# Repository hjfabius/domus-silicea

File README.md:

## Introduction

The Domus Silicea project aims at providing an  integration platform for all things around home automation. 
It is designed to be as hardware/protocol-agnostic as possible. Domus Silicea brings together different bus systems, hardware devices and interface protocols by dedicated bindings. These bindings send and receive commands and status updates on the event bus. This concept allows designing user interfaces with a unique look&feel, but with the possibility to operate devices based on a big number of different technologies. 
Besides the user interfaces, it also brings the power of automation logics across different system boundaries.

## Trademark Disclaimer

Product names, logos, brands and other trademarks referred to within the Domus Silicea website are the property of their respective trademark holders. These trademark holders are not affiliated with Domus Silicea or our website. They do not sponsor or endorse our materials.

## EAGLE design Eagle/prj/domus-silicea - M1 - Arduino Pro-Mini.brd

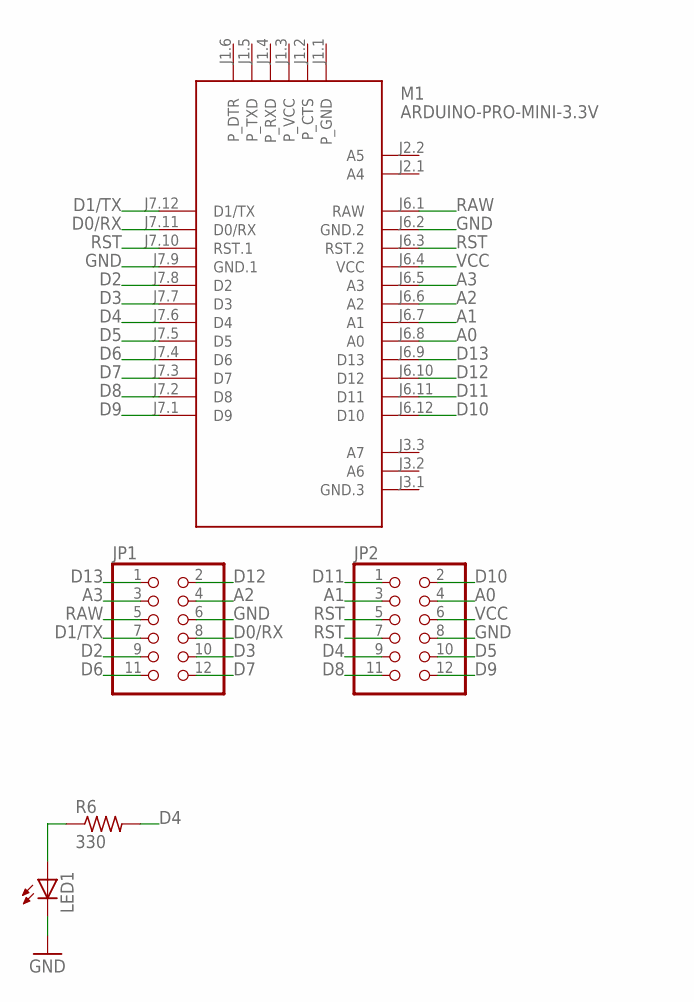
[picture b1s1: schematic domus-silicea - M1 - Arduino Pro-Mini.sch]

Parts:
JP1, JP2: PINHD-2X6; 2X06
LED1: LED5MM
M1: ARDUINO-PRO-MINI-3.3V; ARDUINO-PRO-MINI
R6: 330; 0204/7

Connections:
A0: JP2.4, M1.J6.8 (A0)
A1: JP2.3, M1.J6.7 (A1)
A2: JP1.4, M1.J6.6 (A2)
A3: JP1.3, M1.J6.5 (A3)
D0/RX: JP1.8, M1.J7.11 (D0/RX)
D1/TX: JP1.7, M1.J7.12 (D1/TX)
D2: JP1.9, M1.J7.8 (D2)
D3: JP1.10, M1.J7.7 (D3)
D4: JP2.9, M1.J7.6 (D4), R6.2
D5: JP2.10, M1.J7.5 (D5)
D6: JP1.11, M1.J7.4 (D6)
D7: JP1.12, M1.J7.3 (D7)
D8: JP2.11, M1.J7.2 (D8)
D9: JP2.12, M1.J7.1 (D9)
D10: JP2.2, M1.J6.12 (D10)
D11: JP2.1, M1.J6.11 (D11)
D12: JP1.2, M1.J6.10 (D12)
D13: JP1.1, M1.J6.9 (D13)
GND: JP1.6, JP2.8, LED1.K (C), M1.J6.2 (GND.2), M1.J7.9 (GND.1)
unnamed: LED1.A, R6.1
RAW: JP1.5, M1.J6.1 (RAW)
RST: JP2.5, JP2.7, M1.J6.3 (RST.2), M1.J7.10 (RST.1)
VCC: JP2.6, M1.J6.4 (VCC)

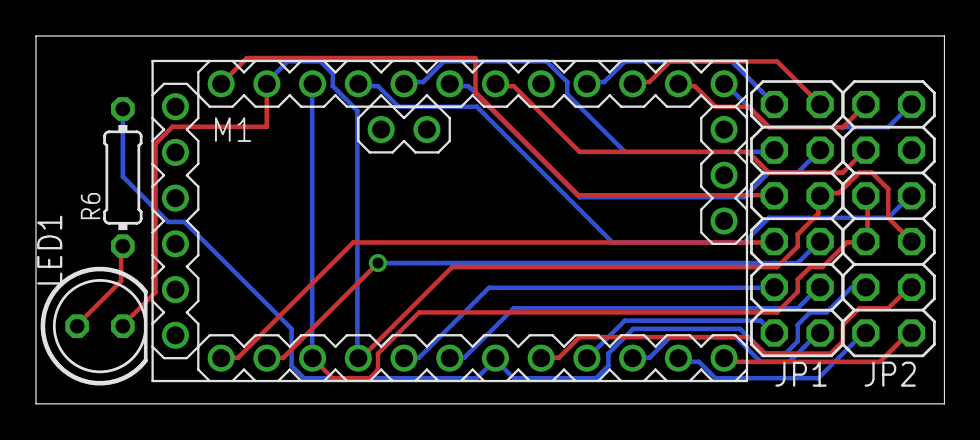
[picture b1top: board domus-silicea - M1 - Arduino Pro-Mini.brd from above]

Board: 2 copper layers, 50.5 x 20.4 mm, 5 parts (0 on the bottom side), 23 nets.

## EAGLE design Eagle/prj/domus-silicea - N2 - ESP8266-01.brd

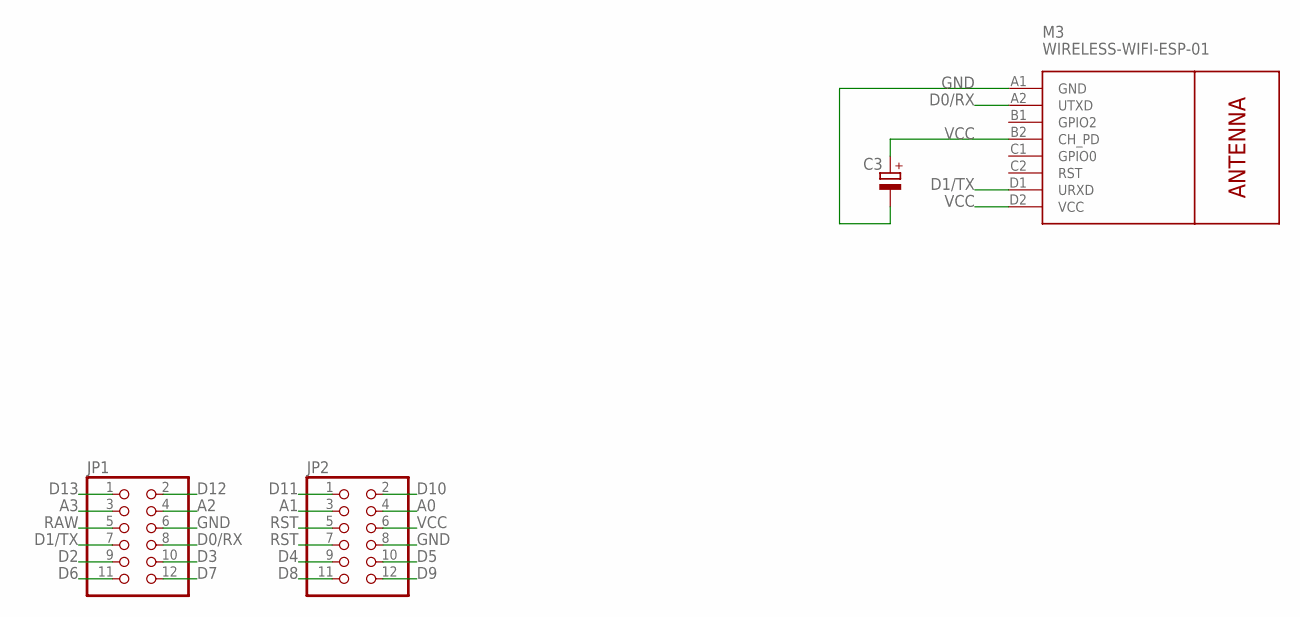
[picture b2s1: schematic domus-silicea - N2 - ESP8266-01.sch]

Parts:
C3: CPOL-EUE2,5-6E; E2,5-6E
JP1, JP2: PINHD-2X6; 2X06
M3: WIRELESS-WIFI-ESP-01

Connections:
A0: JP2.4
A1: JP2.3
A2: JP1.4
A3: JP1.3
D0/RX: JP1.8, M3.A2 (UTXD)
D1/TX: JP1.7, M3.D1 (URXD)
D2: JP1.9
D3: JP1.10
D4: JP2.9
D5: JP2.10
D6: JP1.11
D7: JP1.12
D8: JP2.11
D9: JP2.12
D10: JP2.2
D11: JP2.1
D12: JP1.2
D13: JP1.1
GND: C3.-, JP1.6, JP2.8, M3.A1 (GND)
RAW: JP1.5
RST: JP2.5, JP2.7
VCC: C3.+, JP2.6, M3.B2 (CH_PD), M3.D2 (VCC)

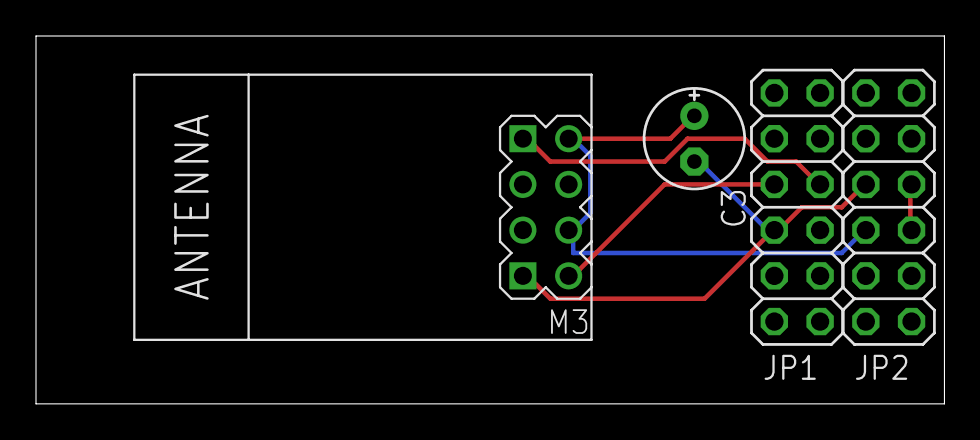
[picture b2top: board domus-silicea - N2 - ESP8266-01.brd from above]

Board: 2 copper layers, 50.5 x 20.4 mm, 4 parts (0 on the bottom side), 5 nets.

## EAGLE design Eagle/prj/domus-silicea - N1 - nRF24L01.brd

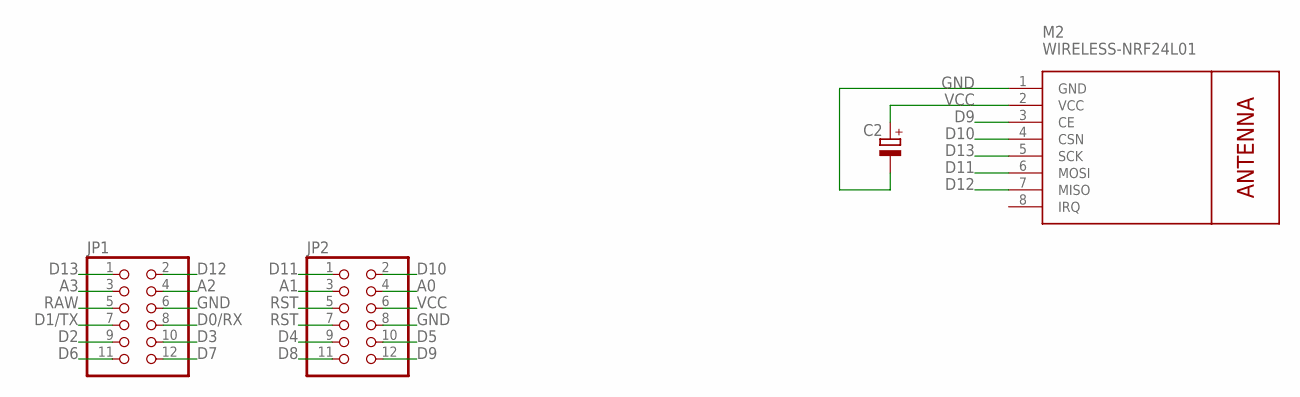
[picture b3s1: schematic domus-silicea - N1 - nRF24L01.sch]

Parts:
C2: CPOL-EUE2,5-6E; E2,5-6E
JP1, JP2: PINHD-2X6; 2X06
M2: WIRELESS-NRF24L01

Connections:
A0: JP2.4
A1: JP2.3
A2: JP1.4
A3: JP1.3
D0/RX: JP1.8
D1/TX: JP1.7
D2: JP1.9
D3: JP1.10
D4: JP2.9
D5: JP2.10
D6: JP1.11
D7: JP1.12
D8: JP2.11
D9: JP2.12, M2.3 (CE)
D10: JP2.2, M2.4 (CSN)
D11: JP2.1, M2.6 (MOSI)
D12: JP1.2, M2.7 (MISO)
D13: JP1.1, M2.5 (SCK)
GND: C2.-, JP1.6, JP2.8, M2.1 (GND)
RAW: JP1.5
RST: JP2.5, JP2.7
VCC: C2.+, JP2.6, M2.2 (VCC)

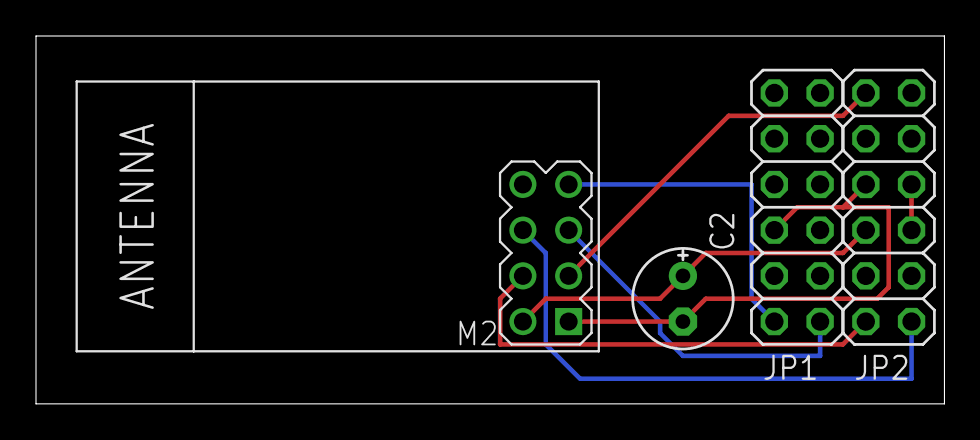
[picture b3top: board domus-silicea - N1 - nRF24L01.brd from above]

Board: 2 copper layers, 50.5 x 20.4 mm, 4 parts (0 on the bottom side), 8 nets.

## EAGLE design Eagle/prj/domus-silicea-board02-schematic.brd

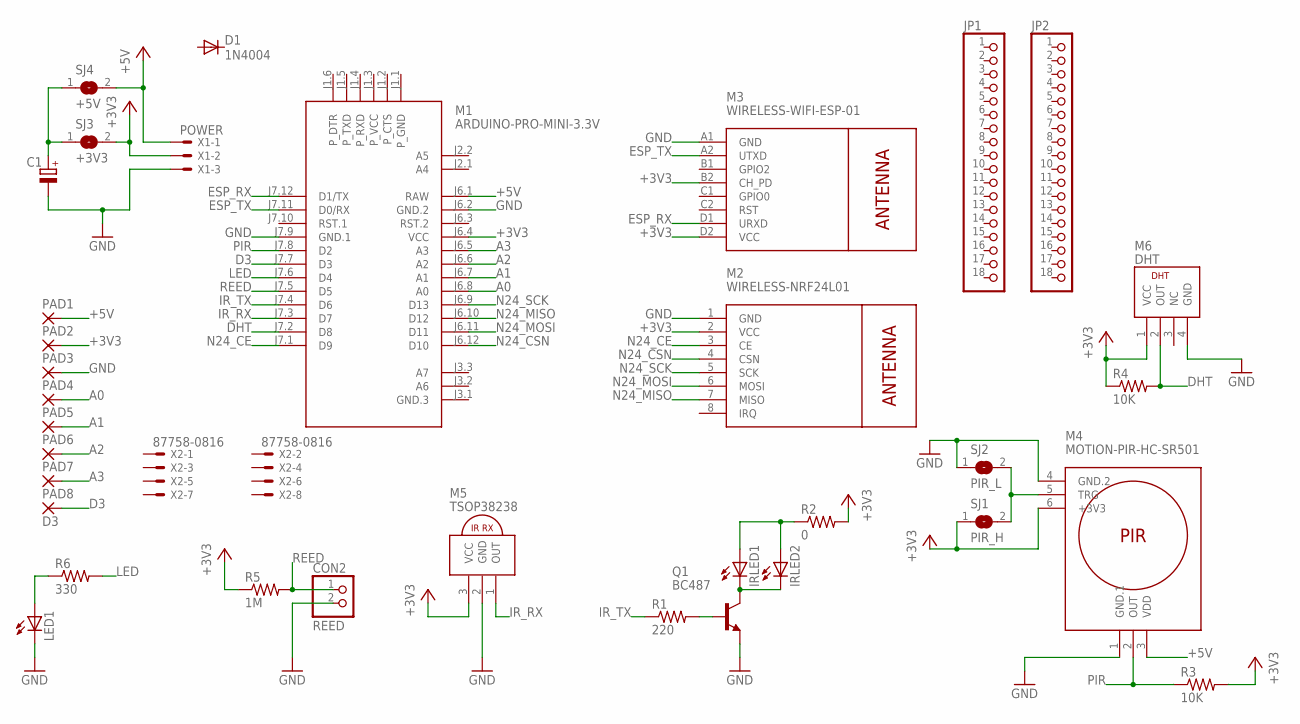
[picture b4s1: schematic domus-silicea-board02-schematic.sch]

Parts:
C1: CPOL-EUE2,5-6E; E2,5-6E
CON2: REED; 1X02
D1: 1N4004; DO41-10
IRLED1, IRLED2: LED5MM
JP1, JP2: PINHD-1X18; 1X18
LED1: LED5MM
M1: ARDUINO-PRO-MINI-3.3V; ARDUINO-PRO-MINI
M2: WIRELESS-NRF24L01
M3: WIRELESS-WIFI-ESP-01
M4: MOTION-PIR-HC-SR501
M5: TSOP38238
M6: DHT
PAD1, PAD2, PAD3, PAD4, PAD5, PAD6, PAD7: 2,54/1,0
PAD8: D3; 2,54/1,0
Q1: BC487; TO92-EBC
R1: 220; 0204/7
R2: 0; 0204/7
R3, R4: 10K; 0204/7
R5: 1M; 0204/7
R6: 330; 0204/7
SJ1: PIR_H; SJ
SJ2: PIR_L; SJ
SJ3: +3V3; SJ
SJ4: +5V; SJ
X1: POWER; 22-23-2031; MPN POWER
X2: 87758-0816

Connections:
+3V3: M1.J6.4 (VCC), M2.2 (VCC), M3.B2 (CH_PD), M3.D2 (VCC), M4.6 (+3V3), M5.3 (VCC), M6.1 (VCC), PAD2.1, R2.2, R3.2, R4.1, R5.1, SJ1.1, SJ3.2, X1.2
+5V: M1.J6.1 (RAW), M4.3 (VDD), PAD1.1, SJ4.2, X1.1
A0: M1.J6.8 (A0), PAD4.1
A1: M1.J6.7 (A1), PAD5.1
A2: M1.J6.6 (A2), PAD6.1
A3: M1.J6.5 (A3), PAD7.1
D3: M1.J7.7 (D3), PAD8.1
DHT: M1.J7.2 (D8), M6.2 (OUT), R4.2
ESP_RX: M1.J7.12 (D1/TX), M3.D1 (URXD)
ESP_TX: M1.J7.11 (D0/RX), M3.A2 (UTXD)
GND: C1.-, CON2.2, LED1.K (C), M1.J6.2 (GND.2), M1.J7.9 (GND.1), M2.1 (GND), M3.A1 (GND), M4.1 (GND.1), M4.4 (GND.2), M5.2 (GND), M6.4 (GND), PAD3.1, Q1.E, SJ2.1, X1.3
IR_RX: M1.J7.3 (D7), M5.1 (OUT)
IR_TX: M1.J7.4 (D6), R1.1
LED: M1.J7.6 (D4), R6.2
N24_CE: M1.J7.1 (D9), M2.3 (CE)
N24_CSN: M1.J6.12 (D10), M2.4 (CSN)
N24_MISO: M1.J6.10 (D12), M2.7 (MISO)
N24_MOSI: M1.J6.11 (D11), M2.6 (MOSI)
N24_SCK: M1.J6.9 (D13), M2.5 (SCK)
unnamed: IRLED1.K (C), IRLED2.K (C), Q1.C
unnamed: IRLED1.A, IRLED2.A, R2.1
unnamed: Q1.B, R1.2
unnamed: C1.+, SJ3.1, SJ4.1
unnamed: M4.5 (TRG), SJ1.2, SJ2.2
unnamed: LED1.A, R6.1
PIR: M1.J7.8 (D2), M4.2 (OUT), R3.1
REED: CON2.1, M1.J7.5 (D5), R5.2

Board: 2 copper layers, 35 parts (0 on the bottom side), 27 nets, no tracks yet.

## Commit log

2015-01-13 GIT initialization
2015-01-13 Substitution of standard README.md
2015-02-14 Kicad
2015-02-23 Raspbmc
2015-02-28 Teleboy Repository
2015-03-01 Dell off
2015-03-03 public-website
2015-03-04 Kicad - LIRC Raspberry
2015-03-12 Step 31
2015-06-15 Fritzing
2015-06-16 Fritzing 2
2015-06-22 EasyIot
2015-06-30 EASYIOT_TEMP_V3 - Pir
2015-07-07 IR Led Strip
2015-07-14 EasyIot v6 - Led Strip
2015-07-22 EasyIot v7
2015-07-23 EasyIot v8
2015-07-24 EasyIot_v9
2015-08-03 Fritzing PIR
2015-08-05 Eagle
2015-08-07 Eagle New Path
2015-08-11 Eagle_Board
2015-08-14 Packaging
2015-08-14 domus-silicea - M1 - Arduino Pro-Mini
2015-10-04 EASYIOT_OLED
2015-12-13 OpenHab
2016-01-07 Openhab 23
2016-01-08 GDrive Sync
2016-01-10 NodeMCU
2016-01-10 openhab_reboot.sh
2016-01-11 check file age before download it
2016-01-12 usbLinux
2016-01-14 NodeMCU gasMeter
2016-01-30 NodeMCU - V1
2016-01-31 NodeMCU v1
2016-01-31 NodeMCU v2
2016-02-02 NodeMCU 3.0
2016-02-04 NodeMCU v4
2016-02-06 Openhab 1.8
2016-02-06 NodeMCU v5
2016-02-06 Tentative SQLLite (not fully working
2016-02-14 Gas Alarm
2016-02-17 NodeMCU v6
2016-02-19 Water Items
2016-02-24 Openhab MySQL
2016-02-27 Kodi Favorites
2016-03-05 NodeMCU v8
2016-03-05 Openhab 1.8.1 - NAS
2016-03-07 NodeMCU v9
2016-03-07 RGB led
2016-03-17 Openhab - Weather
2016-03-17 ESPduino - MQTT
2016-03-18 Openhab - Link Temperature Gas
2016-04-12 FF_LivingRoom_v10
2016-06-02 FF_BedRoom_v11

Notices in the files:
parts and their libraries:
diy-modules: Released under the Creative Commons Attribution 4.0 International License: http://creativecommons.org/licenses/by/4.0
